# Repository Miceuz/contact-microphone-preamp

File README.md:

# contact-microphone-preamp
A preamplifier for contact microphone. Input impedance ~400k Ohm. Low cut at ~5Hz. Based on low power and extremely low noise opamp 
ADA4084 by Analog Devices.

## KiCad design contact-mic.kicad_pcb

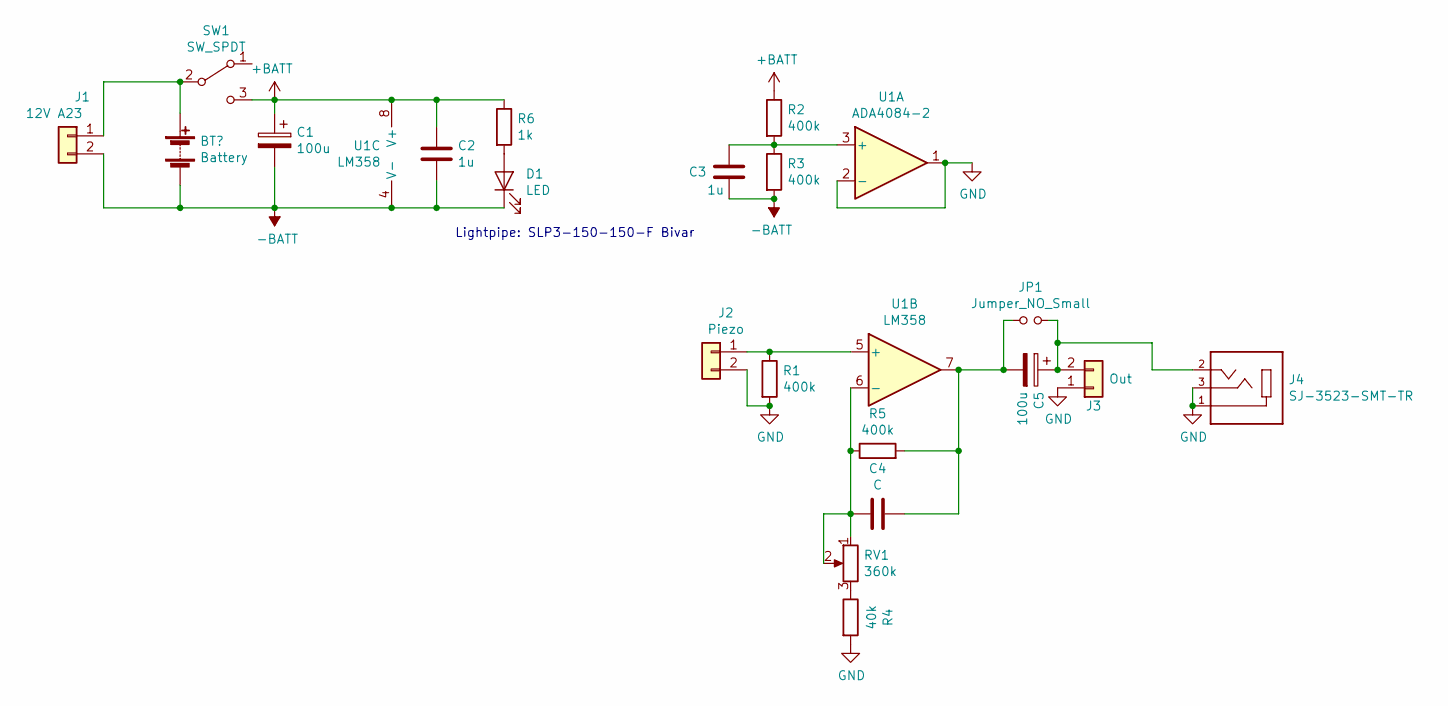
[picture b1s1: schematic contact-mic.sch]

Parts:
C1, C5: 100u; CP_Elec_6.3x7.7; PartNo EEE-HC1C101XP
C2, C3: 1u; C_0603_1608Metric
C4: C; C_0603_1608Metric
D1: LED; LED_0603_SLP3-150-150-F
J1: 12V A23; Pin_Header_Straight_1x02_Pitch2.54mm
J2: Piezo; Pin_Header_Straight_1x02_Pitch2.54mm; PartNo CEB-44D06
J3: Out; Pin_Header_Straight_1x02_Pitch2.54mm
J4: SJ-3523-SMT-TR; CUI_SJ-3523-SMT-TR; PartNo SJ-3523-SMT-TR
JP1: Jumper_NO_Small; SolderJumper-2_P1.3mm_Open_RoundedPad1.0x1.5mm
R1, R2, R3, R5: 400k; R_0603_1608Metric
R4: 40k; R_0603_1608Metric
R6: 1k; R_0603_1608Metric
RV1: 360k; Trimpot_3.8mmx3.6mm_TC33X-2-103E; PartNo TC33X-2-304E
SW1: SW_SPDT; SW_SPDT_PCM12; PartNo PCM12SMTR
U1: ADA4084-2; SO-8_3.9x4.9mm_P1.27mm; PartNo ADA4084-2ARZ-R7

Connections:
+BATT: C1.1, C2.2, R2.1, R6.1, SW1.3 (C), U1.8 (V+)
-BATT: C1.2, C2.1, C3.2, D1.1 (K), J1.2, R3.2, U1.4 (V-); also elsewhere on the board
GND: J2.2, J3.1, J4.1, J4.3, R1.2, R4.2, U1.1, U1.2 (-)
unnamed 3: J1.1, SW1.2 (B); also elsewhere on the board
unnamed: C3.1, R2.2, R3.1, U1.3 (+)
unnamed: C4.1, C5.2, JP1.1, R5.2, U1.7
unnamed: C4.2, R5.1, RV1.1, RV1.2, U1.6 (-)
unnamed: C5.1, J3.2, J4.2, JP1.2
unnamed: D1.2 (A), R6.2
unnamed: J2.1, R1.1, U1.5 (+)
unnamed: R4.1, RV1.3

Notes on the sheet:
Lightpipe: SLP3-150-150-F Bivar

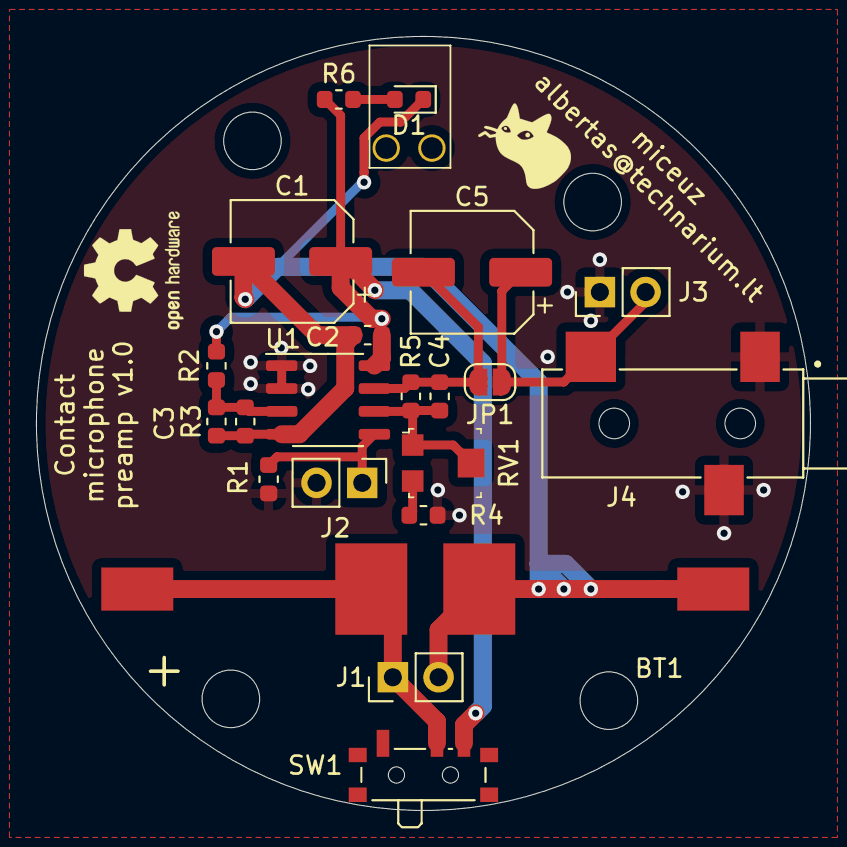
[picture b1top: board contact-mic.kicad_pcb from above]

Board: 2 copper layers, 43.0 x 43.0 mm, 21 parts (0 on the bottom side), 11 nets.

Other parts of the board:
BT1: Battery; A23_BATT

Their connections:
-BATT: BT1.2; also elsewhere on the board
unnamed 3: BT1.1; also elsewhere on the board

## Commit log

2019-08-06 Initial
2019-08-06 Add all the stuff
2019-08-06 Add illustration
